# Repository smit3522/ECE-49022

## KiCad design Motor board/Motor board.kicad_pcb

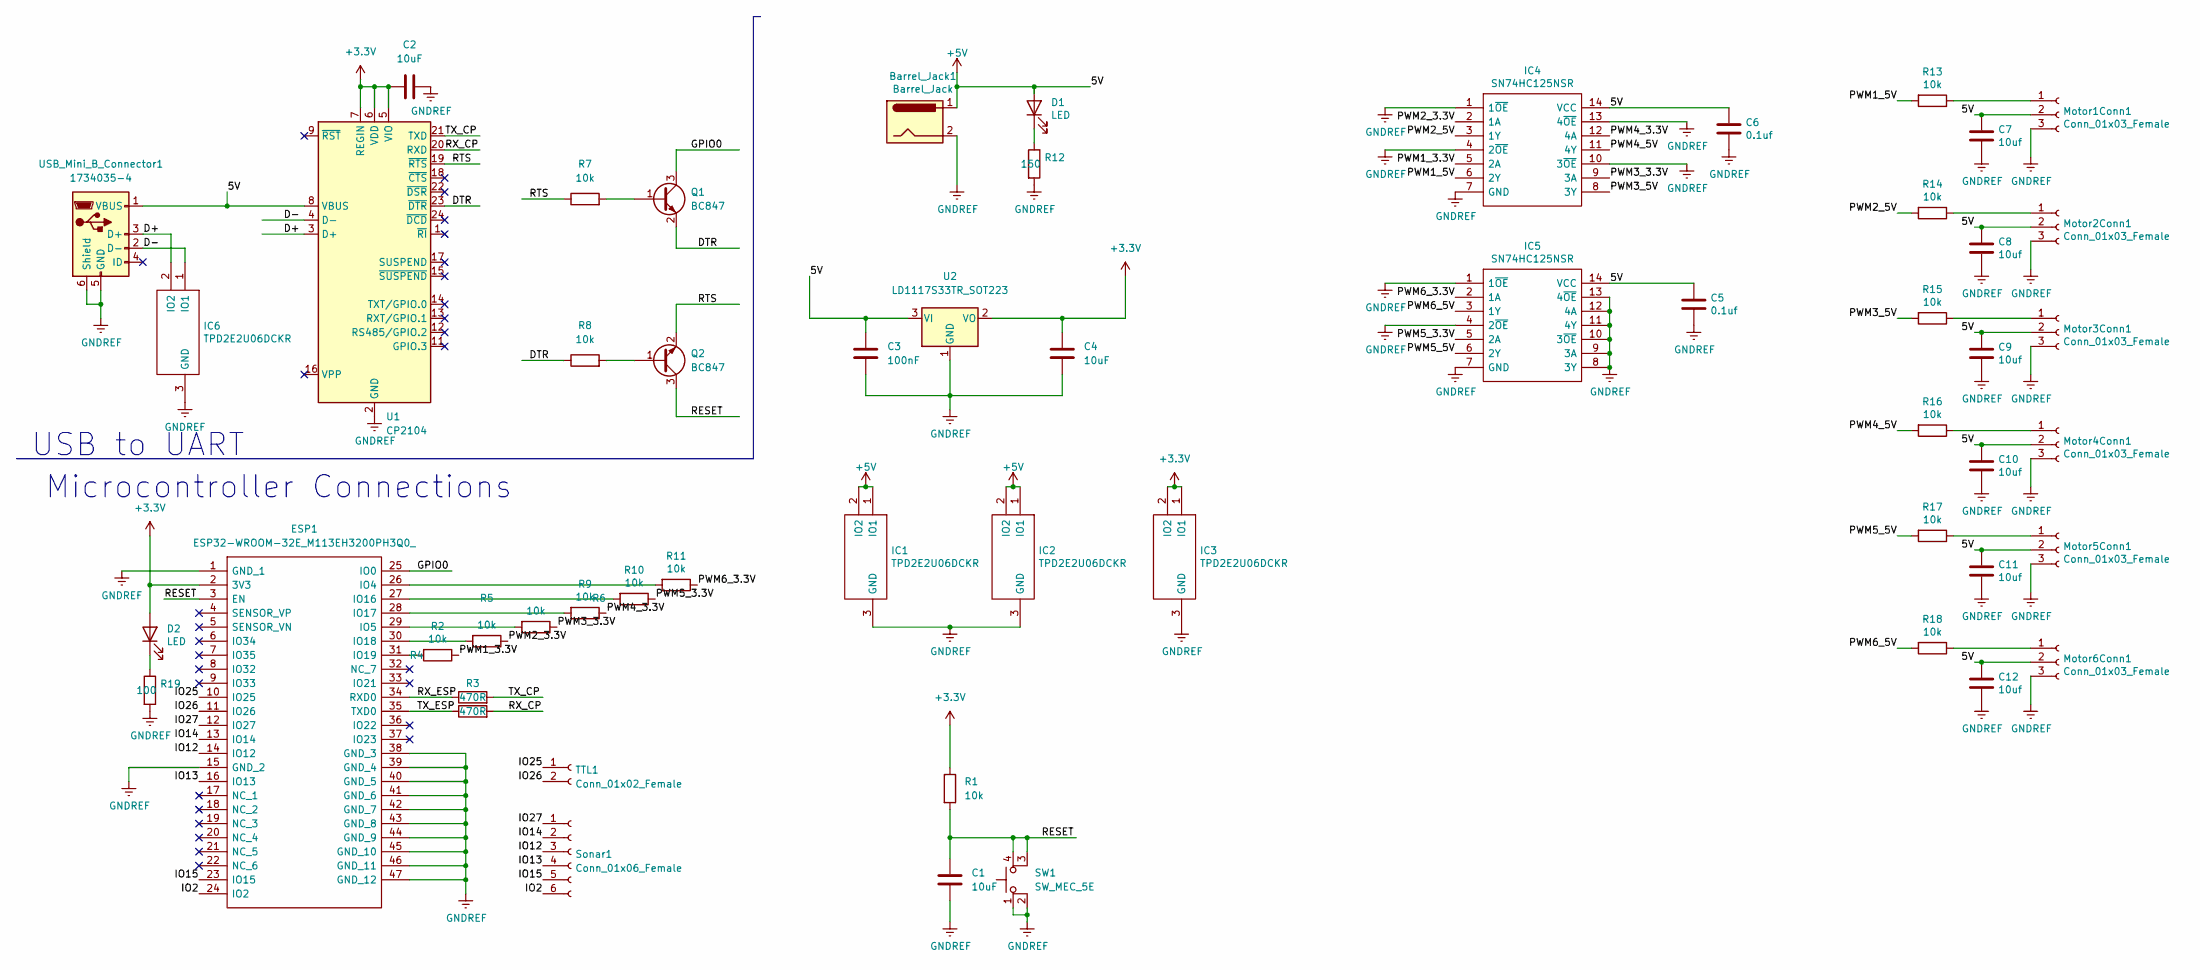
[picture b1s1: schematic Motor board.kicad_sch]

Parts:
Barrel_Jack1: Barrel_Jack; BarrelJack_CUI_PJ-063AH_Horizontal_CircularHoles
C1, C2, C4: 10uF; C_0805_2012Metric_Pad1.18x1.45mm_HandSolder
C3: 100nF; C_0805_2012Metric_Pad1.18x1.45mm_HandSolder
C5, C6: 0.1uf; C_0805_2012Metric
C7, C8, C9, C10, C11, C12: 10uf; C_0805_2012Metric
D1, D2: LED; LED_D3.0mm_FlatTop
ESP1: ESP32-WROOM-32E_M113EH3200PH3Q0_; ESP32WROOM32EM113EH3200PH3Q0; Mouser Part Number 356-ESP32WRM32E132PH
IC1, IC2, IC3, IC6: TPD2E2U06DCKR; TPD; Mouser Part Number 595-TPD2E2U06DCKR
IC4, IC5: SN74HC125NSR; SN74; Mouser Part Number 595-SN74HC125NSR
Motor1Conn1, Motor2Conn1, Motor3Conn1, Motor4Conn1, Motor5Conn1, Motor6Conn1: Conn_01x03_Female; PinSocket_1x03_P2.54mm_Vertical
Q1, Q2: BC847; SOT-23
R1, R2, R5, R6, R7, R8, R9, R10, R11, R13, R14, R15, R16, R17, R18: 10k; R_0805_2012Metric_Pad1.20x1.40mm_HandSolder
R3, R4: 470R; R_0805_2012Metric_Pad1.20x1.40mm_HandSolder
R12: 150; R_0805_2012Metric_Pad1.20x1.40mm_HandSolder
R19: 100; R_0805_2012Metric_Pad1.20x1.40mm_HandSolder
SW1: SW_MEC_5E; SW_TH_Tactile_Omron_B3F-10xx
Sonar1: Conn_01x06_Female; PinHeader_1x06_P2.54mm_Vertical
TTL1: Conn_01x02_Female; PinHeader_1x02_P2.54mm_Vertical
U1: CP2104; QFN-24-1EP_4x4mm_P0.5mm_EP2.6x2.6mm
U2: LD1117S33TR_SOT223; SOT-223-3_TabPin2
USB_Mini_B_Connector1: 1734035-4; USB_Mini-B_Wuerth_65100516121_Horizontal

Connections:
+3V3: C2.1, C4.1, D2.2 (A), ESP1.2 (3V3), IC3.1 (IO1), IC3.2 (IO2), R1.1, U1.5 (VIO), U1.6 (VDD), U1.7 (REGIN), U2.2 (VO)
+5V: Barrel_Jack1.1, C3.1, C5.1, C6.1, C7.1, C8.1, C9.1, C10.1, C11.1, C12.1, D1.2 (A), IC1.1 (IO1), IC1.2 (IO2), IC2.1 (IO1), IC2.2 (IO2), IC4.14 (VCC), IC5.14 (VCC), Motor1Conn1.2, Motor2Conn1.2, Motor3Conn1.2, Motor4Conn1.2, Motor5Conn1.2, Motor6Conn1.2, U1.8 (VBUS), U2.3 (VI), USB_Mini_B_Connector1.1 (VBUS)
/D+: IC6.2 (IO2), U1.3 (D+), USB_Mini_B_Connector1.3 (D+)
/D-: IC6.1 (IO1), U1.4 (D-), USB_Mini_B_Connector1.2 (D-)
/DTR: Q1.2 (E), R8.1, U1.23 (~DTR)
/GPIO0: ESP1.25 (IO0), Q1.3 (C)
/IO2: ESP1.24 (IO2), Sonar1.6
/IO12: ESP1.14 (IO12), Sonar1.3
/IO13: ESP1.16 (IO13), Sonar1.4
/IO14: ESP1.13 (IO14), Sonar1.2
/IO15: ESP1.23 (IO15), Sonar1.5
/IO25: ESP1.10 (IO25), TTL1.1
/IO26: ESP1.11 (IO26), TTL1.2
/IO27: ESP1.12 (IO27), Sonar1.1
/PWM1_3.3V: IC4.5 (2A), R2.1
/PWM1_5V: IC4.6 (2Y), R13.2
/PWM2_3.3V: IC4.2 (1A), R5.1
/PWM2_5V: IC4.3 (1Y), R14.2
/PWM3_3.3V: IC4.9 (3A), R6.1
/PWM3_5V: IC4.8 (3Y), R15.2
/PWM4_3.3V: IC4.12 (4A), R9.1
/PWM4_5V: IC4.11 (4Y), R16.2
/PWM5_3.3V: IC5.5 (2A), R10.1
/PWM5_5V: IC5.6 (2Y), R17.2
/PWM6_3.3V: IC5.2 (1A), R11.1
/PWM6_5V: IC5.3 (1Y), R18.2
/RESET: C1.1, ESP1.3 (EN), Q2.3 (C), R1.2, SW1.3 (K), SW1.4 (A)
/RTS: Q2.2 (E), R7.1, U1.19 (~RTS)
/RX_CP: R4.2, U1.20 (RXD)
/RX_ESP: ESP1.34 (RXD0), R3.1
/TX_CP: R3.2, U1.21 (TXD)
/TX_ESP: ESP1.35 (TXD0), R4.1
GNDREF: Barrel_Jack1.2, C1.2, C2.2, C3.2, C4.2, C5.2, C6.2, C7.2, C8.2, C9.2, C10.2, C11.2, C12.2, ESP1.1 (GND_1), ESP1.15 (GND_2), ESP1.38 (GND_3), ESP1.39 (GND_4), ESP1.40 (GND_5), ESP1.41 (GND_6), ESP1.42 (GND_7), ESP1.43 (GND_8), ESP1.44 (GND_9), ESP1.45 (GND_10), ESP1.46 (GND_11), ESP1.47 (GND_12), IC1.3 (GND), IC2.3 (GND), IC3.3 (GND), IC4.1 (1~OE), IC4.4 (2~OE), IC4.7 (GND), IC4.10 (3~OE), IC4.13 (4~OE), IC5.1 (1~OE), IC5.4 (2~OE), IC5.7 (GND), IC5.8 (3Y), IC5.9 (3A), IC5.10 (3~OE), IC5.11 (4Y), IC5.12 (4A), IC5.13 (4~OE), IC6.3 (GND), Motor1Conn1.3, Motor2Conn1.3, Motor3Conn1.3, Motor4Conn1.3, Motor5Conn1.3, Motor6Conn1.3, R12.2, R19.2, SW1.1, SW1.2, U1.2 (GND), U1.25 (GND), U2.1 (GND), USB_Mini_B_Connector1.5 (GND), USB_Mini_B_Connector1.6 (Shield)
unnamed: D1.1 (K), R12.1
unnamed: D2.1 (K), R19.1
unnamed: ESP1.26 (IO4), R11.2
unnamed: ESP1.27 (IO16), R10.2
unnamed: ESP1.28 (IO17), R9.2
unnamed: ESP1.29 (IO5), R6.2
unnamed: ESP1.30 (IO18), R5.2
unnamed: ESP1.31 (IO19), R2.2
unnamed: Motor1Conn1.1, R13.1
unnamed: Motor2Conn1.1, R14.1
unnamed: Motor3Conn1.1, R15.1
unnamed: Motor4Conn1.1, R16.1
unnamed: Motor5Conn1.1, R17.1
unnamed: Motor6Conn1.1, R18.1
unnamed: Q1.1 (B), R7.2
unnamed: Q2.1 (B), R8.2

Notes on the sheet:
USB to UART
Microcontroller Connections

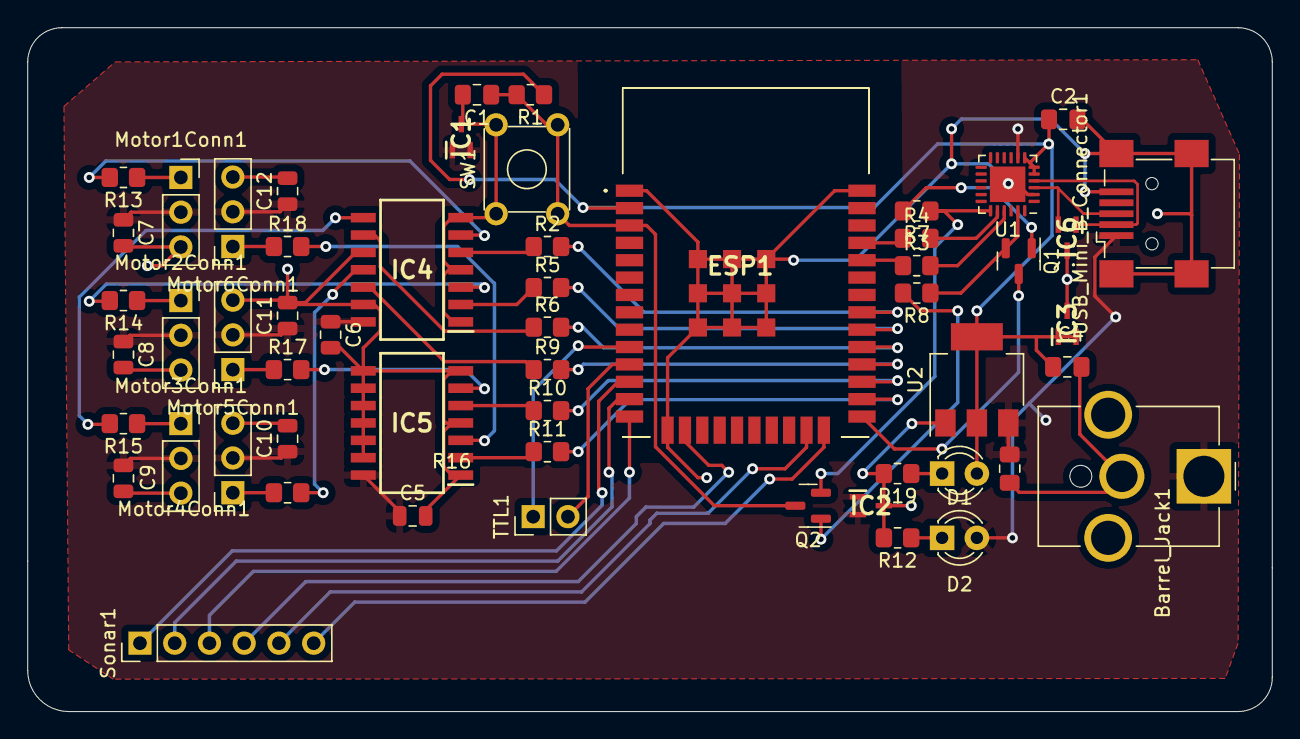
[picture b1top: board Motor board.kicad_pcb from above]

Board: 2 copper layers, 91.0 x 50.0 mm, 55 parts (0 on the bottom side), 49 nets.

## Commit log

2022-01-14 Test.readme
    test file
2022-01-30 Create ESP32
2022-02-04 Bluetooth testing with ESP32
    Read comments in file for assistance.
2022-02-07 KiCad files for ESD401 TVS diode
2022-02-26 Create com_delim_str2array
    Matlab function to convert comma delimited string into integer arrray in matlab
2022-02-26 Rename com_delim_str2array to com_delim_str2array.mat
2022-02-27 Update com_delim_str2array.mat
    Should be working with 3 digits or less now
2022-02-27 Negative numbers work!
2022-02-27 Now works with up to 5 digits, negative or positive
2022-02-27 Motor board PCB
    All system Motor board PCB, still need Brian's stuff
2022-03-02 Motion Control Sim and MAT files
2022-03-03 For Midterm Demo
